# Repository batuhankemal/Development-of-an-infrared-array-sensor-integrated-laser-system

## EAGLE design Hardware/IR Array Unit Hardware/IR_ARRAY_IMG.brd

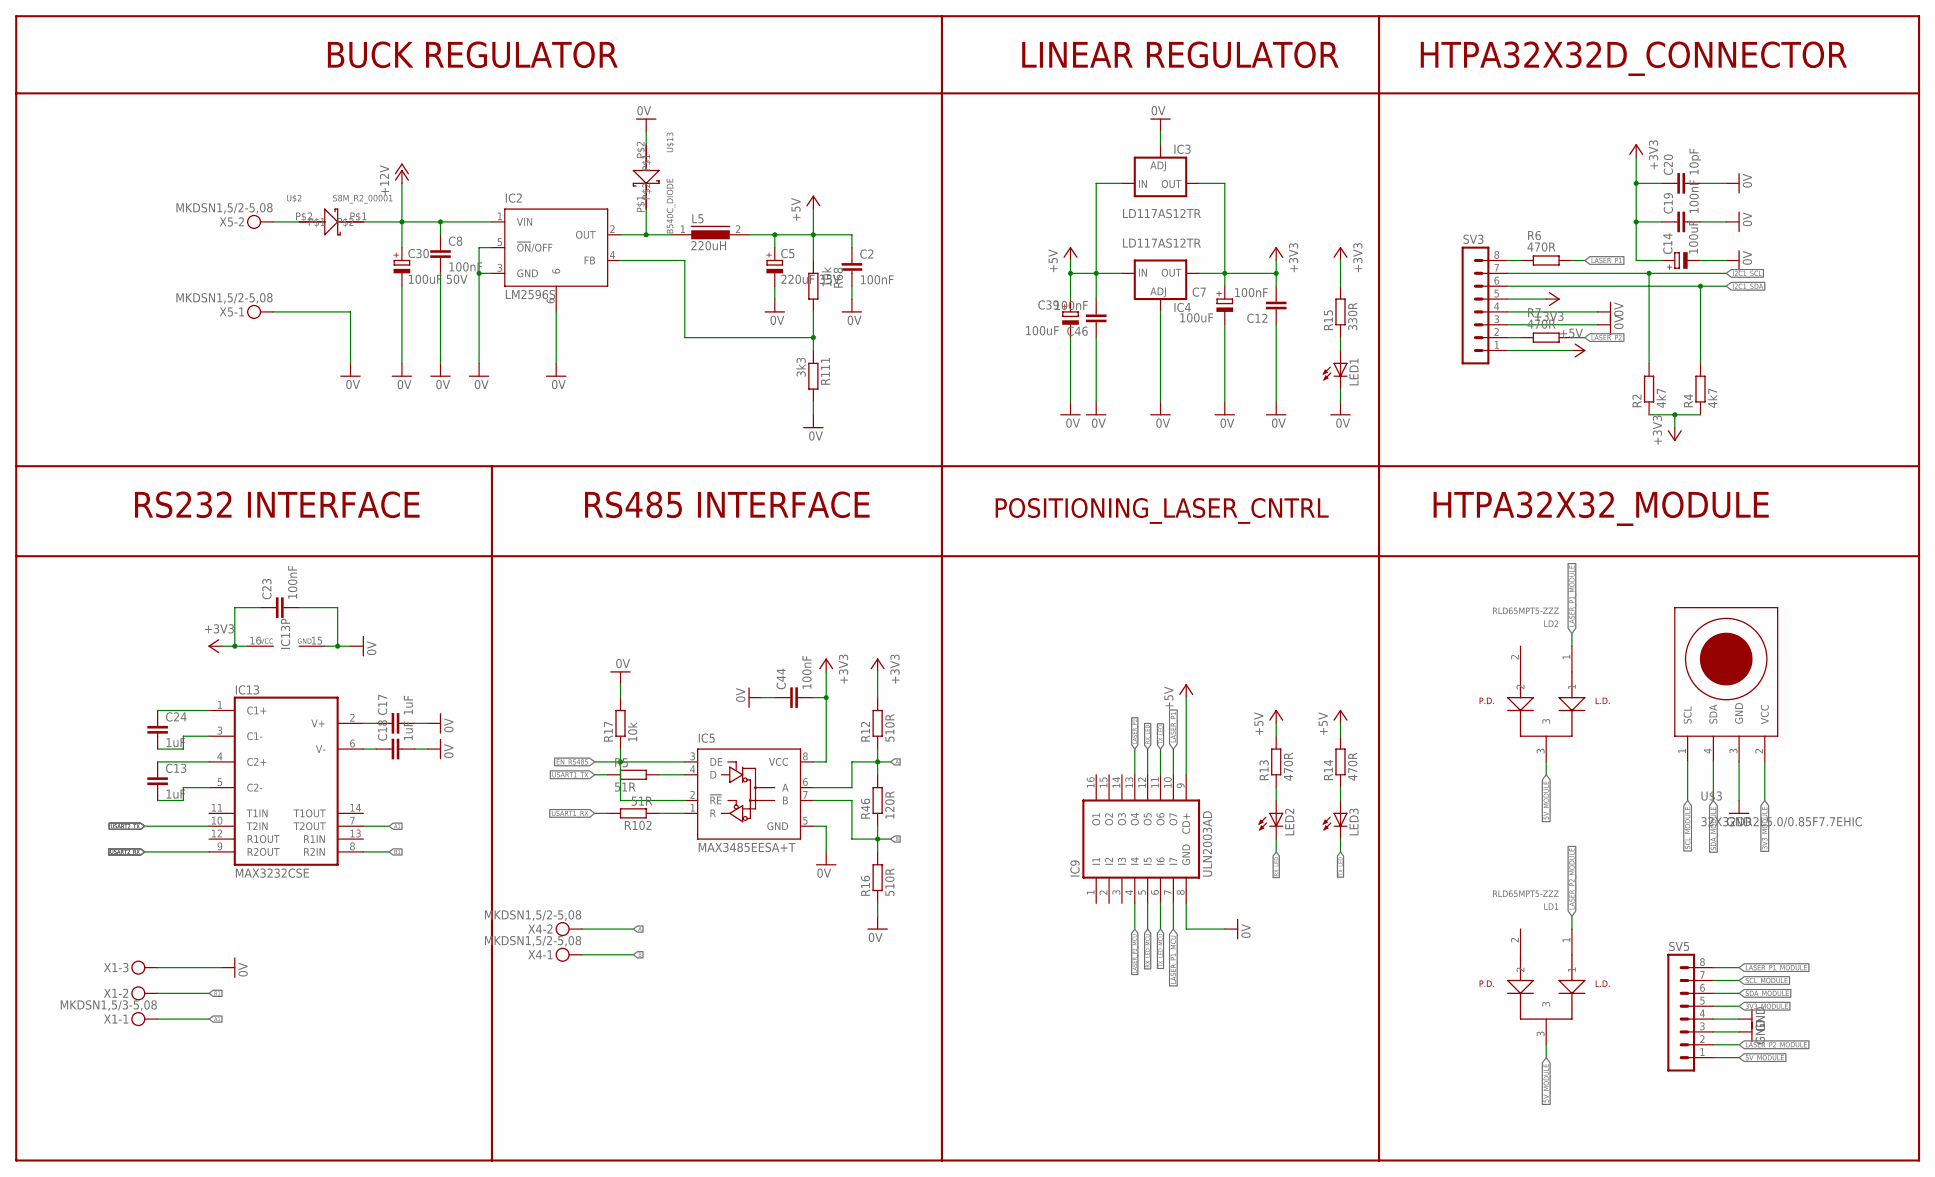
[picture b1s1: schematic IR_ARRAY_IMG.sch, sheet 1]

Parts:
C2, C8: 100nF; C0805
C5: 220uF 35V; 153CLV-0810
C7, C39: 100uF; 153CLV-0605
C12, C19, C23, C44, C46: 100nF; C0603
C13, C17, C18, C24: 1uF; C1206
C14: 100uF; C/6032-28R
C20: 10pF; C0603
C30: 100uF 50V; 153CLV-0810
IC2: LM2596S; TO263-5
IC3, IC4: LD117AS12TR; SOT223
IC5: MAX3485EESA+T; D_R-PDSO-G8
IC9: ULN2003AD; SO16
IC13: MAX3232CSE; SO16
L5: 220uH; DR125
LD1, LD2: RLD65MPT5-ZZZ
LED1, LED2, LED3: LEDCHIPLED_0805; CHIPLED_0805
R2, R4: 4k7; R0603
R5, R102: 51R; R0603
R6, R7: 470R; M0805
R12, R16: 510R; R0603
R13, R14: 470R; R0603
R15: 330R; R0603
R17: 10k; R0603
R46: 120R; R0603
R68: 10k; M0805
R111: 3k3; M0805
SV3, SV5: MA08-1
U$2: S8M_R2_00001; SMC
U$3: 32X32DR2L5.0/0.85F7.7EHIC
U$13: B540C_DIODE; SMC
X1: MKDSN1,5/3-5,08
X4, X5: MKDSN1,5/2-5,08

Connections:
0V: C2.2, C5.-, C7.-, C8.2, C12.1, C14.-, C17.2, C18.2, C19.2, C20.2, C23.2, C30.-, C39.-, C44.1, C46.1, IC2.3 (GND), IC2.5 (!ON!/OFF), IC2.6, IC3.1 (ADJ), IC4.1 (ADJ), IC5.5 (GND), IC9.8 (GND), IC13.15 (GND), LED1.C, R16.1, R17.2, R111.2, SV3.3, SV3.4, U$13.P$2, X1.3, X5.1; also elsewhere on the board
3V3_MODULE: SV5.5, U$3.2 (VCC)
5V_MODULE: LD1.3, LD2.3, SV5.1
+3V3: C7.+, C12.2, C14.+, C19.1, C20.1, C23.1, C44.2, IC3.4 (OUT), IC4.4 (OUT), IC5.8 (VCC), IC13.16 (VCC), R2.1, R4.1, R12.2, R15.2, SV3.5; also elsewhere on the board
+5V: C2.1, C5.+, C39.+, C46.2, IC3.3 (IN), IC4.3 (IN), IC9.9 (CD+), L5.2, R13.2, R14.2, R68.1, SV3.1
+12V: C8.1, C30.+, IC2.1 (VIN), U$2.P$1
A: IC5.6 (A), R12.1, R46.2, X4.2
A1: IC13.7 (T2OUT), X1.1
B: IC5.7 (B), R16.2, R46.1, X4.1
B1: IC13.8 (R2IN), X1.2
EN_RS485: IC5.2 (!RE), IC5.3 (DE), R17.1; also elsewhere on the board
GND: SV5.3, SV5.4, U$3.3 (GND)
I2C1_SCL: R2.2, SV3.7; also elsewhere on the board
I2C1_SDA: R4.2, SV3.6; also elsewhere on the board
LASER_P1: IC9.10 (O7), R6.2
LASER_P1_MCU: IC9.7 (I7); also elsewhere on the board
LASER_P1_MODULE: LD2.1, SV5.8
LASER_P2: IC9.13 (O4), R7.2
LASER_P2_MCU: IC9.4 (I4); also elsewhere on the board
LASER_P2_MODULE: LD1.1, SV5.2
unnamed: U$2.P$2, X5.2
unnamed: C18.1, IC13.6 (V-)
unnamed: R7.1, SV3.2
unnamed: R6.1, SV3.8
unnamed: LED2.A, R13.1
unnamed: LED3.A, R14.1
unnamed: IC5.4 (D), R5.2
unnamed: LED1.A, R15.1
unnamed: C24.1, IC13.1 (C1+)
unnamed: C24.2, IC13.3 (C1-)
unnamed: IC5.1 (R), R102.1
unnamed: C13.1, IC13.4 (C2+)
unnamed: C13.2, IC13.5 (C2-)
unnamed: C17.1, IC13.2 (V+)
unnamed: IC2.2 (OUT), L5.1, U$13.P$1
unnamed: IC2.4 (FB), R68.2, R111.1
RX_LED: IC9.12 (O5), LED2.C
RX_LED_MCU: IC9.5 (I5); also elsewhere on the board
SCL_MODULE: SV5.7, U$3.1 (SCL)
SDA_MODULE: SV5.6, U$3.4 (SDA)
TX_LED: IC9.11 (O6), LED3.C
TX_LED_MCU: IC9.6 (I6); also elsewhere on the board
USART1_RX: R102.2; also elsewhere on the board
USART1_TX: R5.1; also elsewhere on the board
USART2_RX: IC13.9 (R2OUT); also elsewhere on the board
USART2_TX: IC13.10 (T2IN); also elsewhere on the board

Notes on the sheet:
BUCK REGULATOR
LINEAR REGULATOR
RS232 INTERFACE
RS485 INTERFACE
HTPA32X32D_CONNECTOR
HTPA32X32_MODULE
POSITIONING_LASER_CNTRL

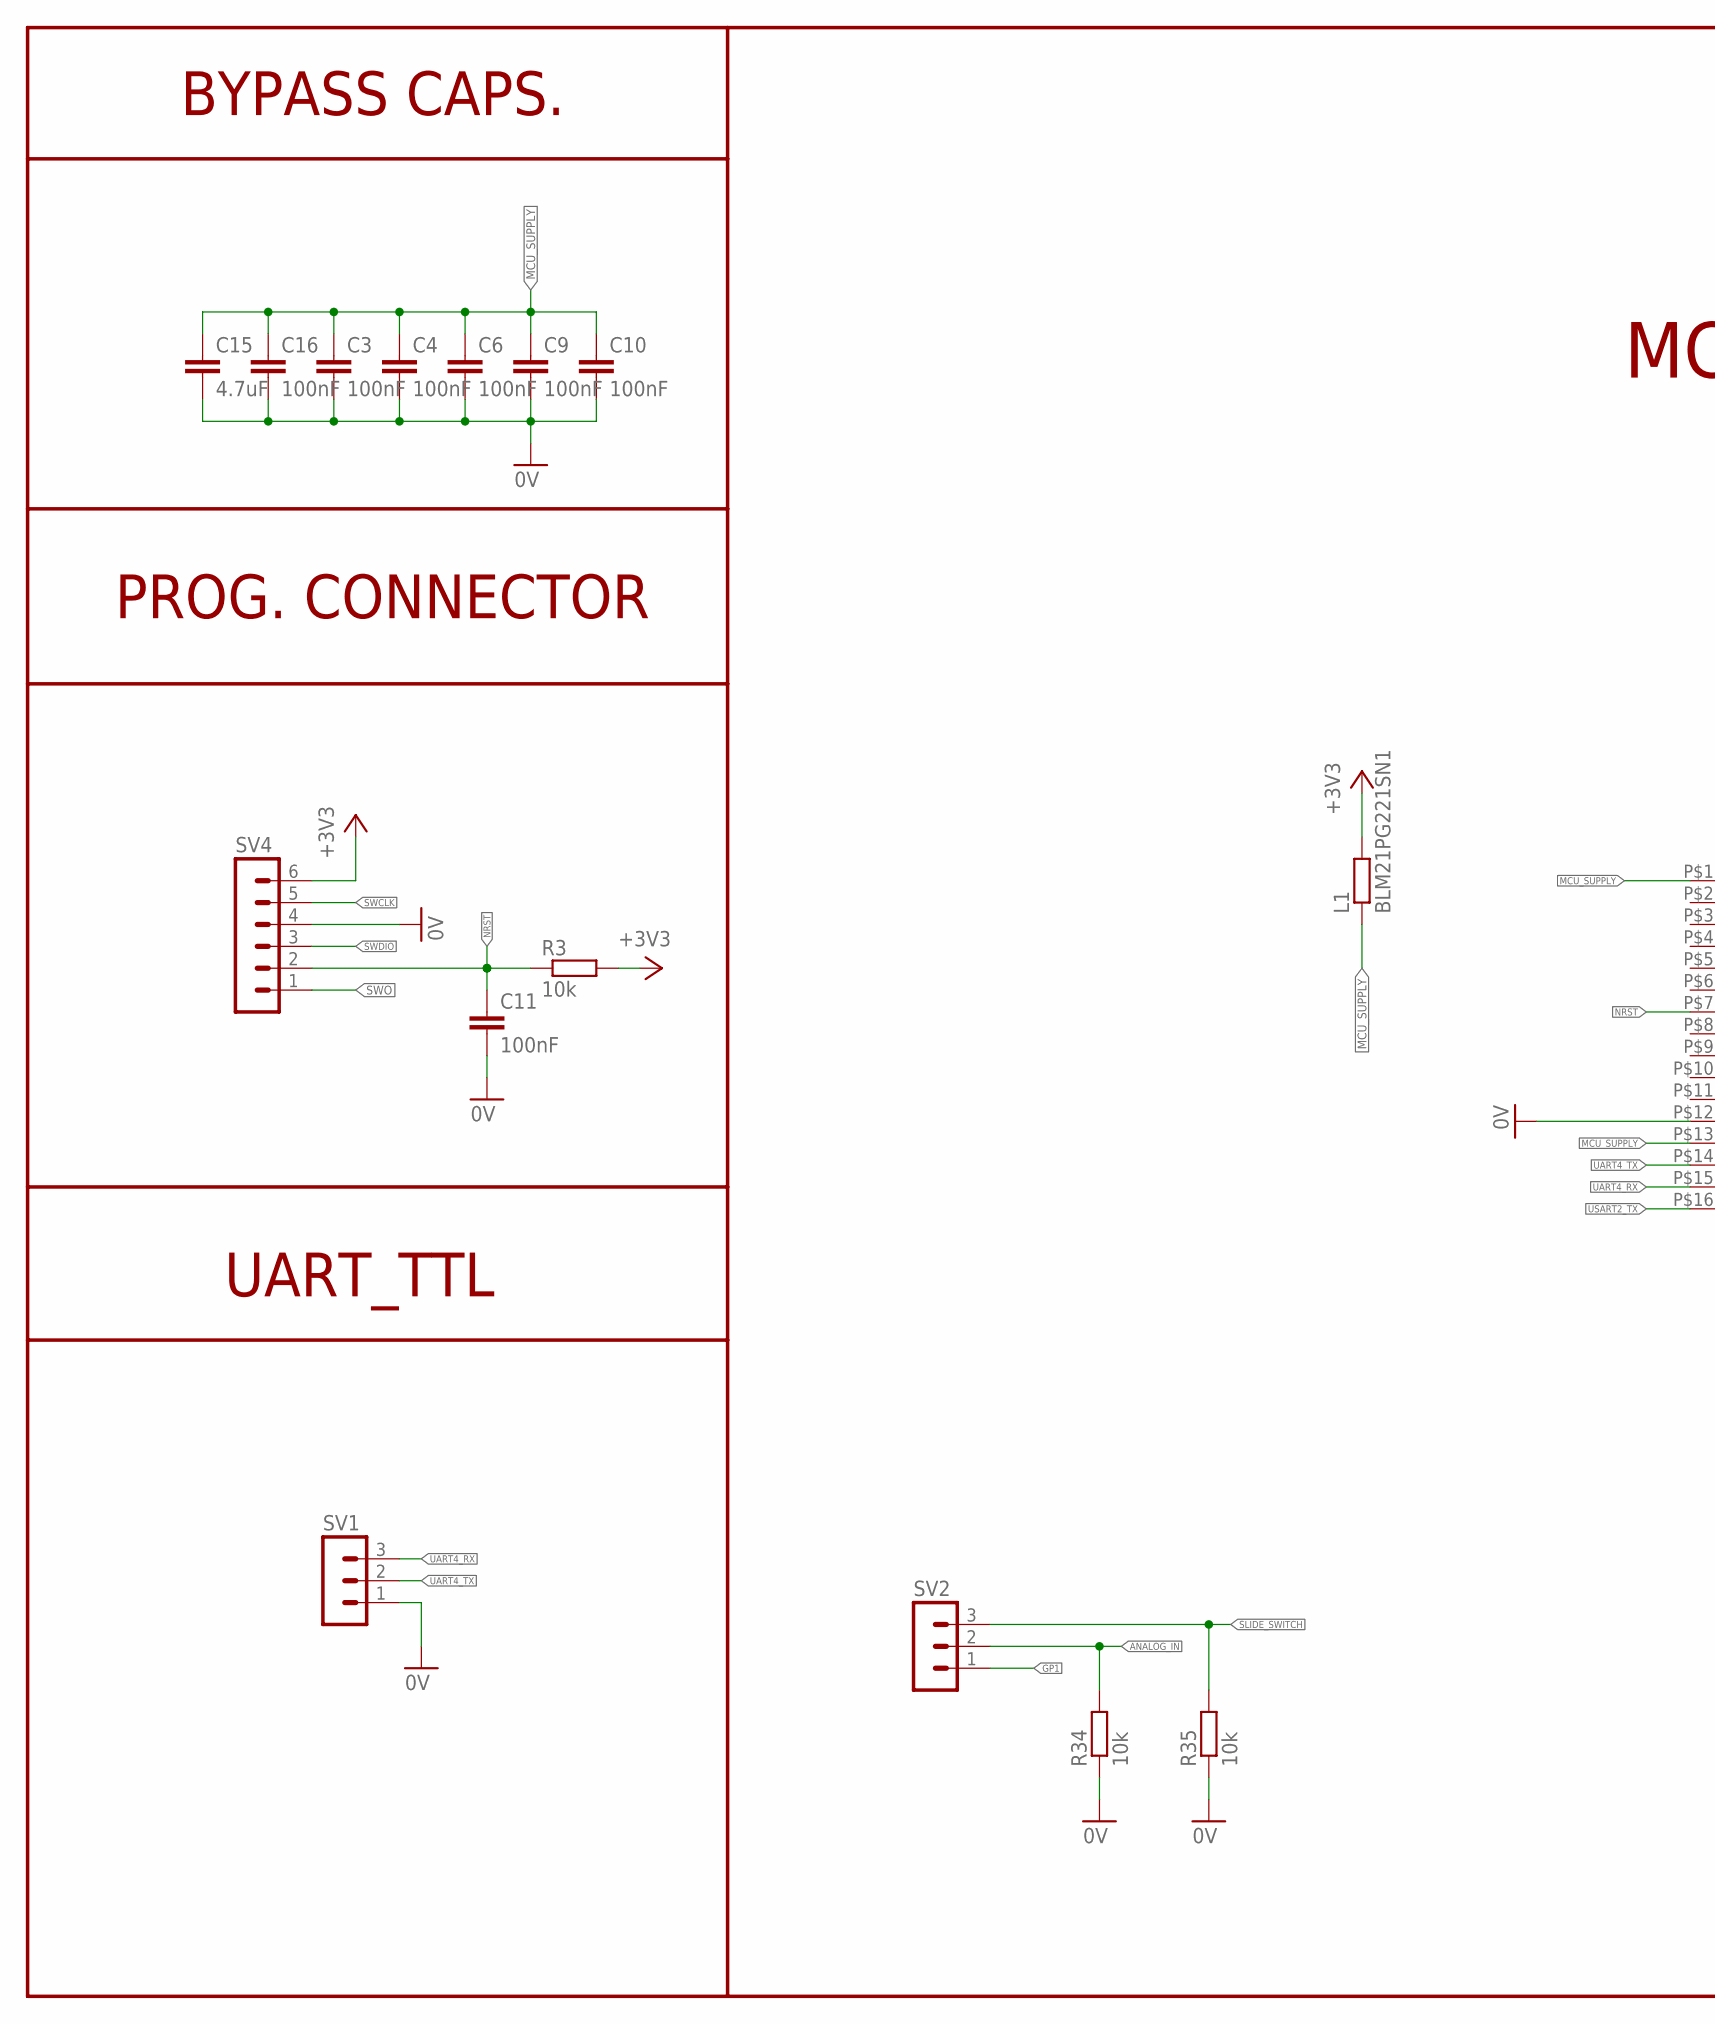
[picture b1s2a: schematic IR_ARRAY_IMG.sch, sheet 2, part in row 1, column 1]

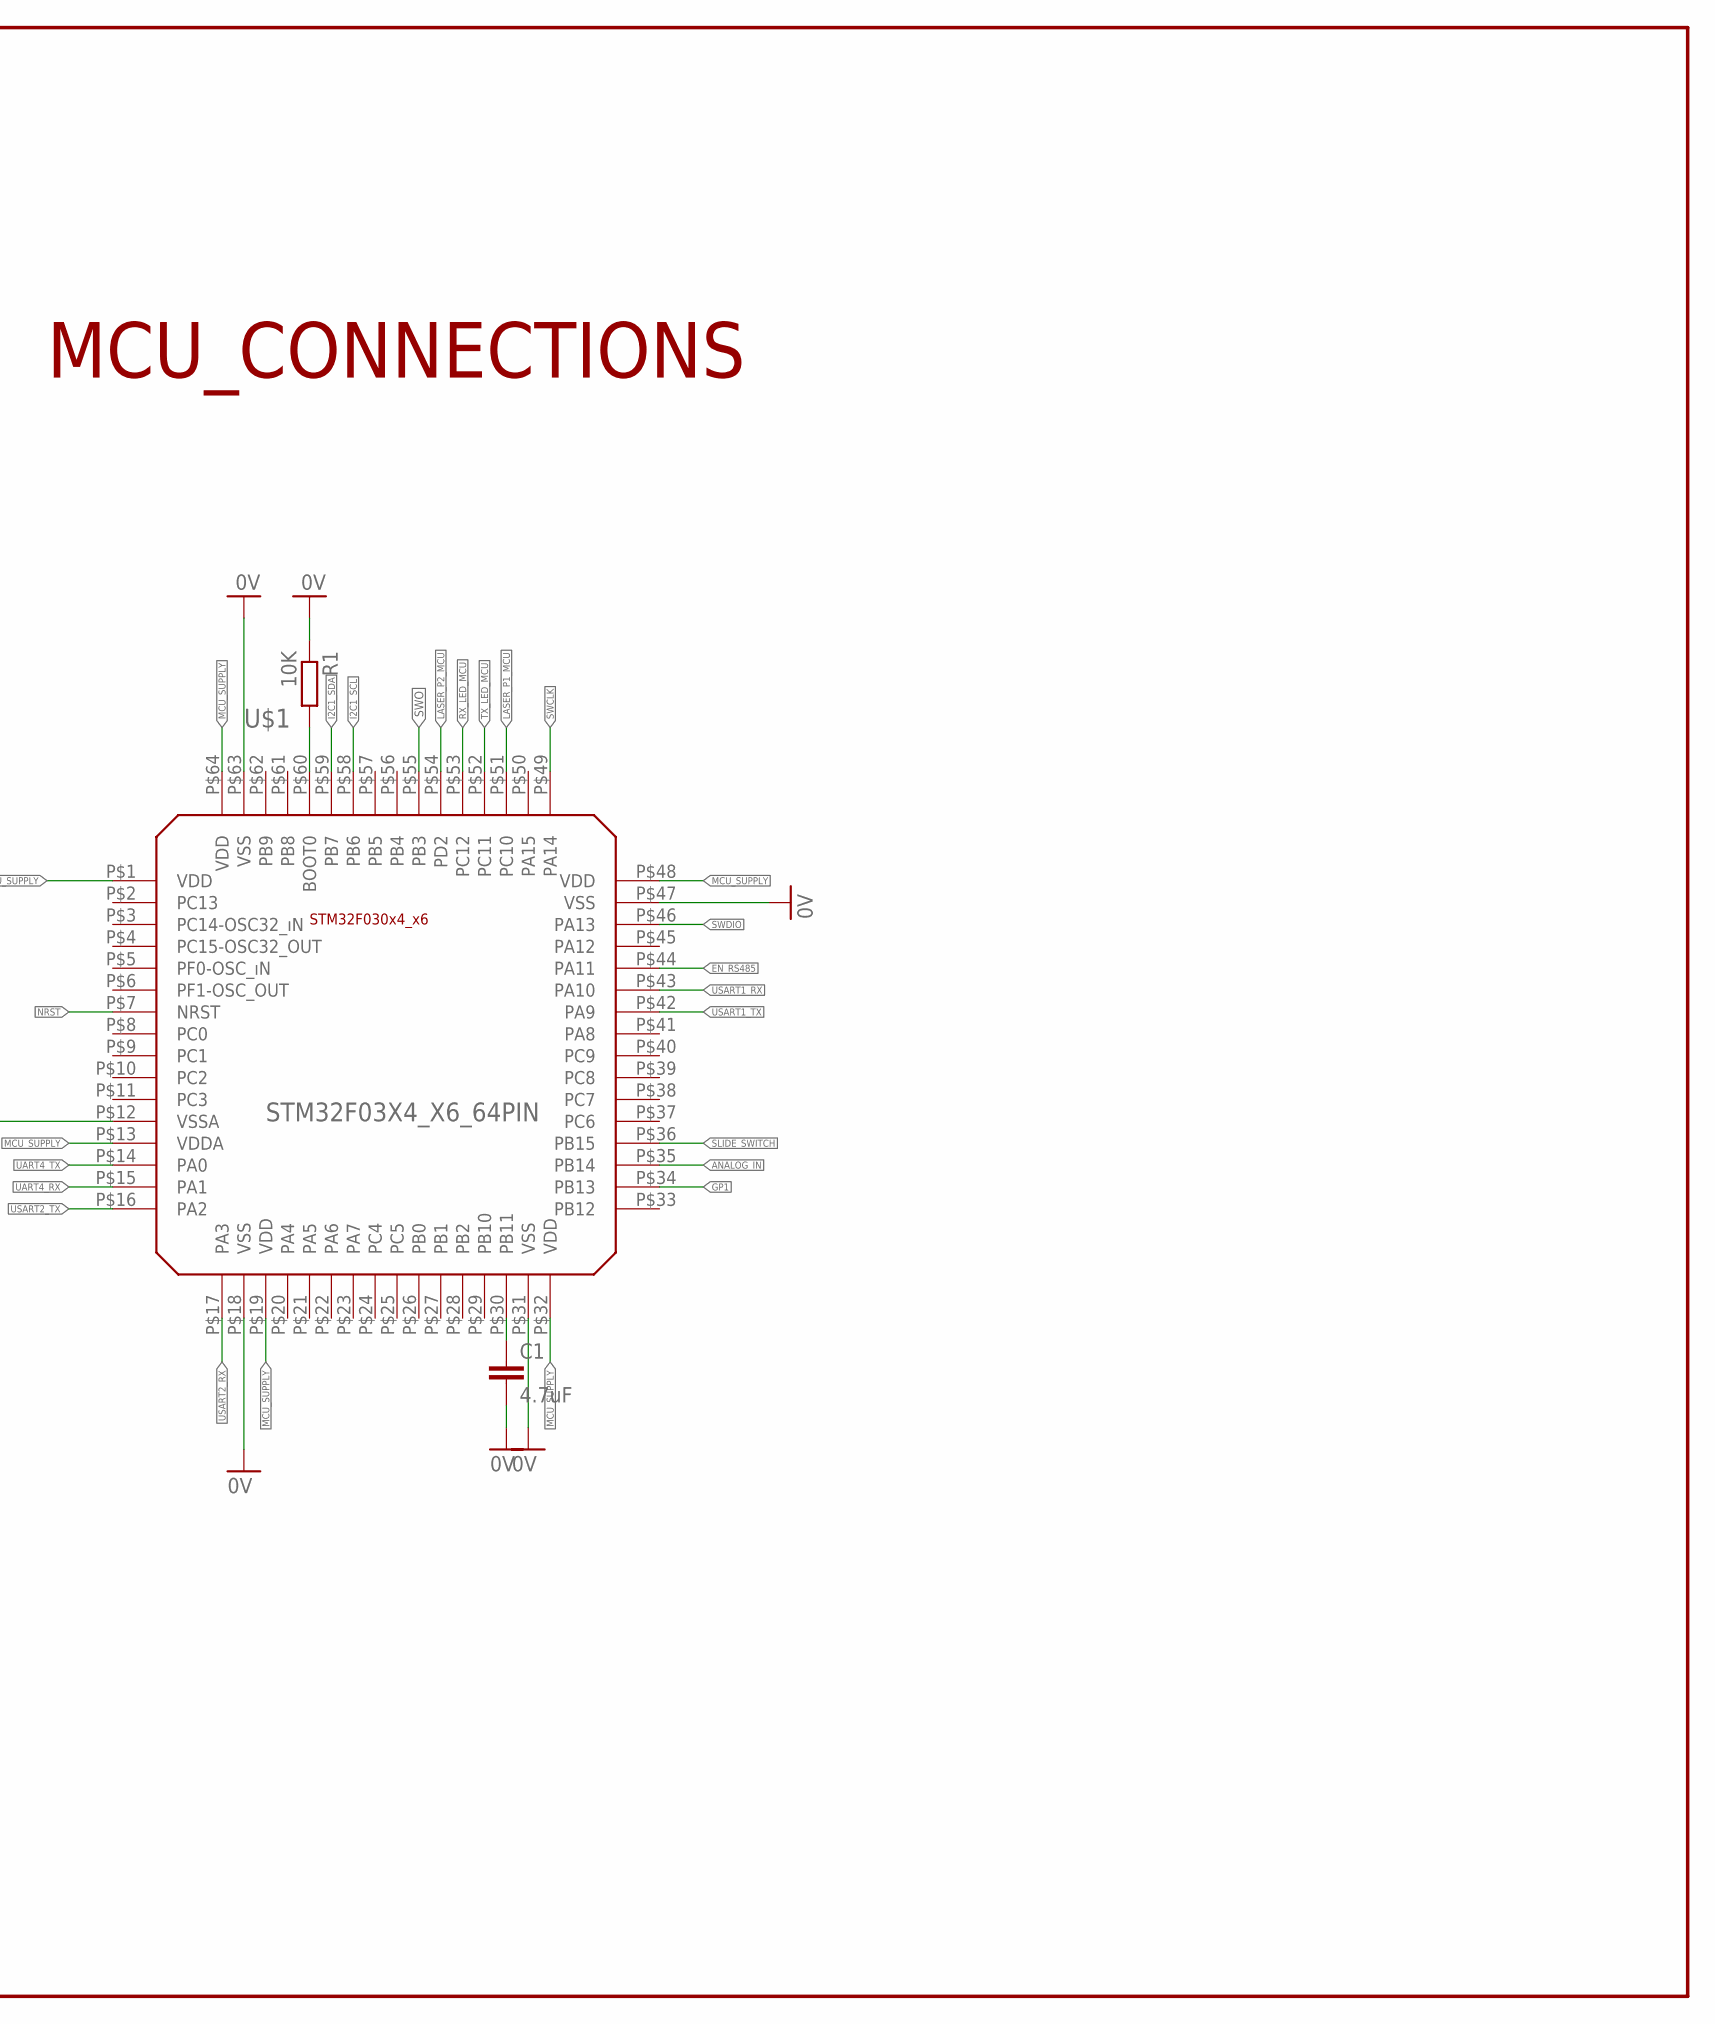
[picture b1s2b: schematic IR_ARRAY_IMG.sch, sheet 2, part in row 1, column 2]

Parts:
C1, C15: 4.7uF; C0805
C3, C4, C6, C9, C10, C11, C16: 100nF; C0603
L1: BLM21PG221SN1; R0805
R1: 10K; R0603
R3, R34, R35: 10k; R0603
SV1, SV2: MA03-1
SV4: MA06-1
U$1: STM32F03X4_X6_64PIN; LQFP64

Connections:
0V: C1.2, C3.2, C4.2, C6.2, C9.2, C10.2, C11.2, C15.2, C16.2, R1.1, R34.1, R35.1, SV1.1, SV4.4, U$1.P$12 (VSSA), U$1.P$18 (VSS), U$1.P$31 (VSS), U$1.P$47 (VSS), U$1.P$63 (VSS); also elsewhere on the board
+3V3: L1.2, R3.2, SV4.6; also elsewhere on the board
ANALOG_IN: R34.2, SV2.2, U$1.P$35 (PB14)
EN_RS485: U$1.P$44 (PA11); also elsewhere on the board
GP1: SV2.1, U$1.P$34 (PB13)
I2C1_SCL: U$1.P$58 (PB6); also elsewhere on the board
I2C1_SDA: U$1.P$59 (PB7); also elsewhere on the board
LASER_P1_MCU: U$1.P$51 (PC10); also elsewhere on the board
LASER_P2_MCU: U$1.P$54 (PD2); also elsewhere on the board
MCU_SUPPLY: C3.1, C4.1, C6.1, C9.1, C10.1, C15.1, C16.1, L1.1, U$1.P$1 (VDD), U$1.P$13 (VDDA), U$1.P$19 (VDD), U$1.P$32 (VDD), U$1.P$48 (VDD), U$1.P$64 (VDD)
unnamed: R1.2, U$1.P$60 (BOOT0)
unnamed: C1.1, U$1.P$30 (PB11)
NRST: C11.1, R3.1, SV4.2, U$1.P$7 (NRST)
RX_LED_MCU: U$1.P$53 (PC12); also elsewhere on the board
SLIDE_SWITCH: R35.2, SV2.3, U$1.P$36 (PB15)
SWCLK: SV4.5, U$1.P$49 (PA14)
SWDIO: SV4.3, U$1.P$46 (PA13)
SWO: SV4.1, U$1.P$55 (PB3)
TX_LED_MCU: U$1.P$52 (PC11); also elsewhere on the board
UART4_RX: SV1.3, U$1.P$15 (PA1)
UART4_TX: SV1.2, U$1.P$14 (PA0)
USART1_RX: U$1.P$43 (PA10); also elsewhere on the board
USART1_TX: U$1.P$42 (PA9); also elsewhere on the board
USART2_RX: U$1.P$17 (PA3); also elsewhere on the board
USART2_TX: U$1.P$16 (PA2); also elsewhere on the board

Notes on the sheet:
BYPASS CAPS.
PROG. CONNECTOR
MCU_CONNECTIONS
UART_TTL

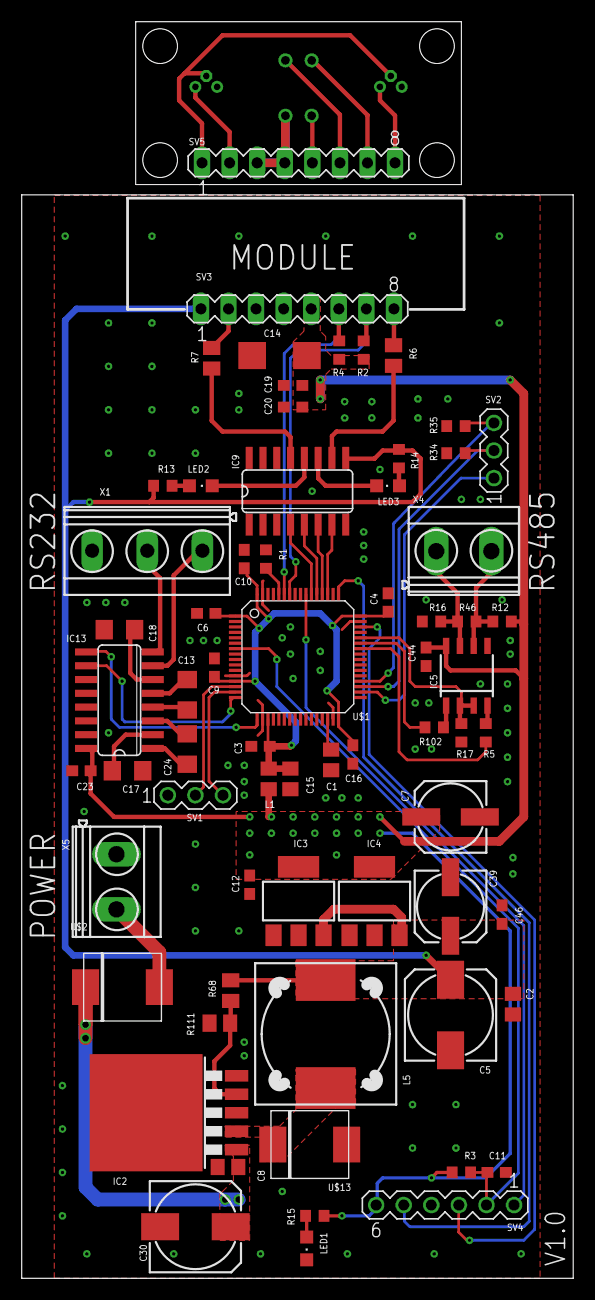
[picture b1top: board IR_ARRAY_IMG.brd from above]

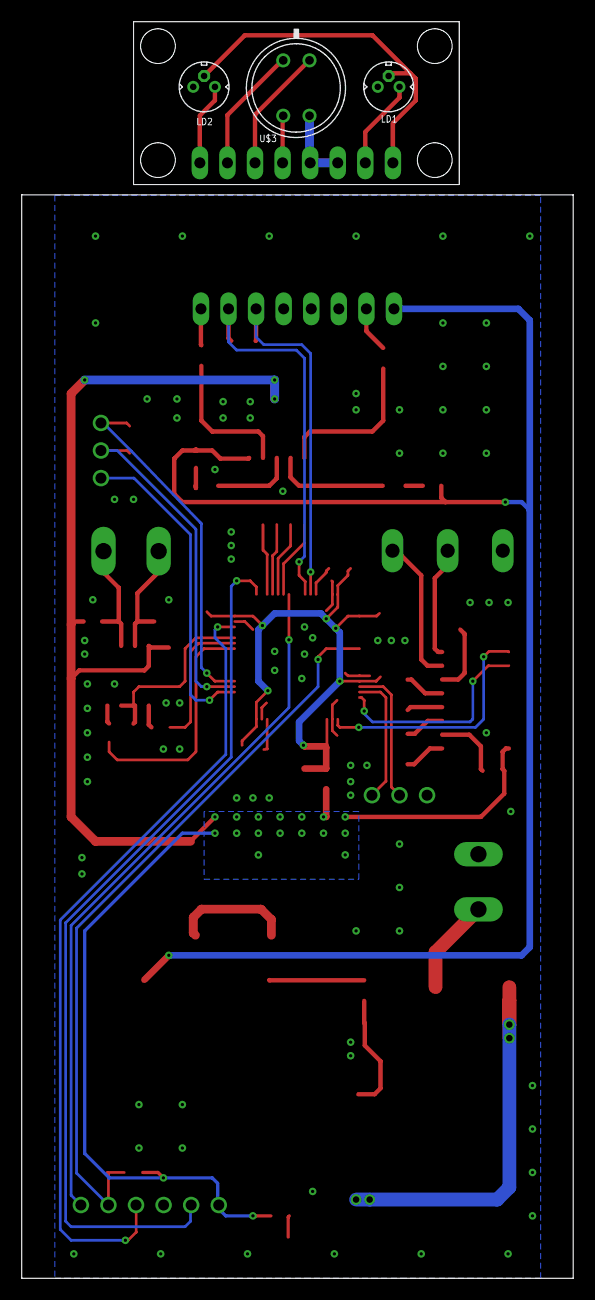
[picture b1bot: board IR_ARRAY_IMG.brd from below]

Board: 2 copper layers, 50.8 x 115.8 mm, 70 parts (3 on the bottom side), 58 nets.

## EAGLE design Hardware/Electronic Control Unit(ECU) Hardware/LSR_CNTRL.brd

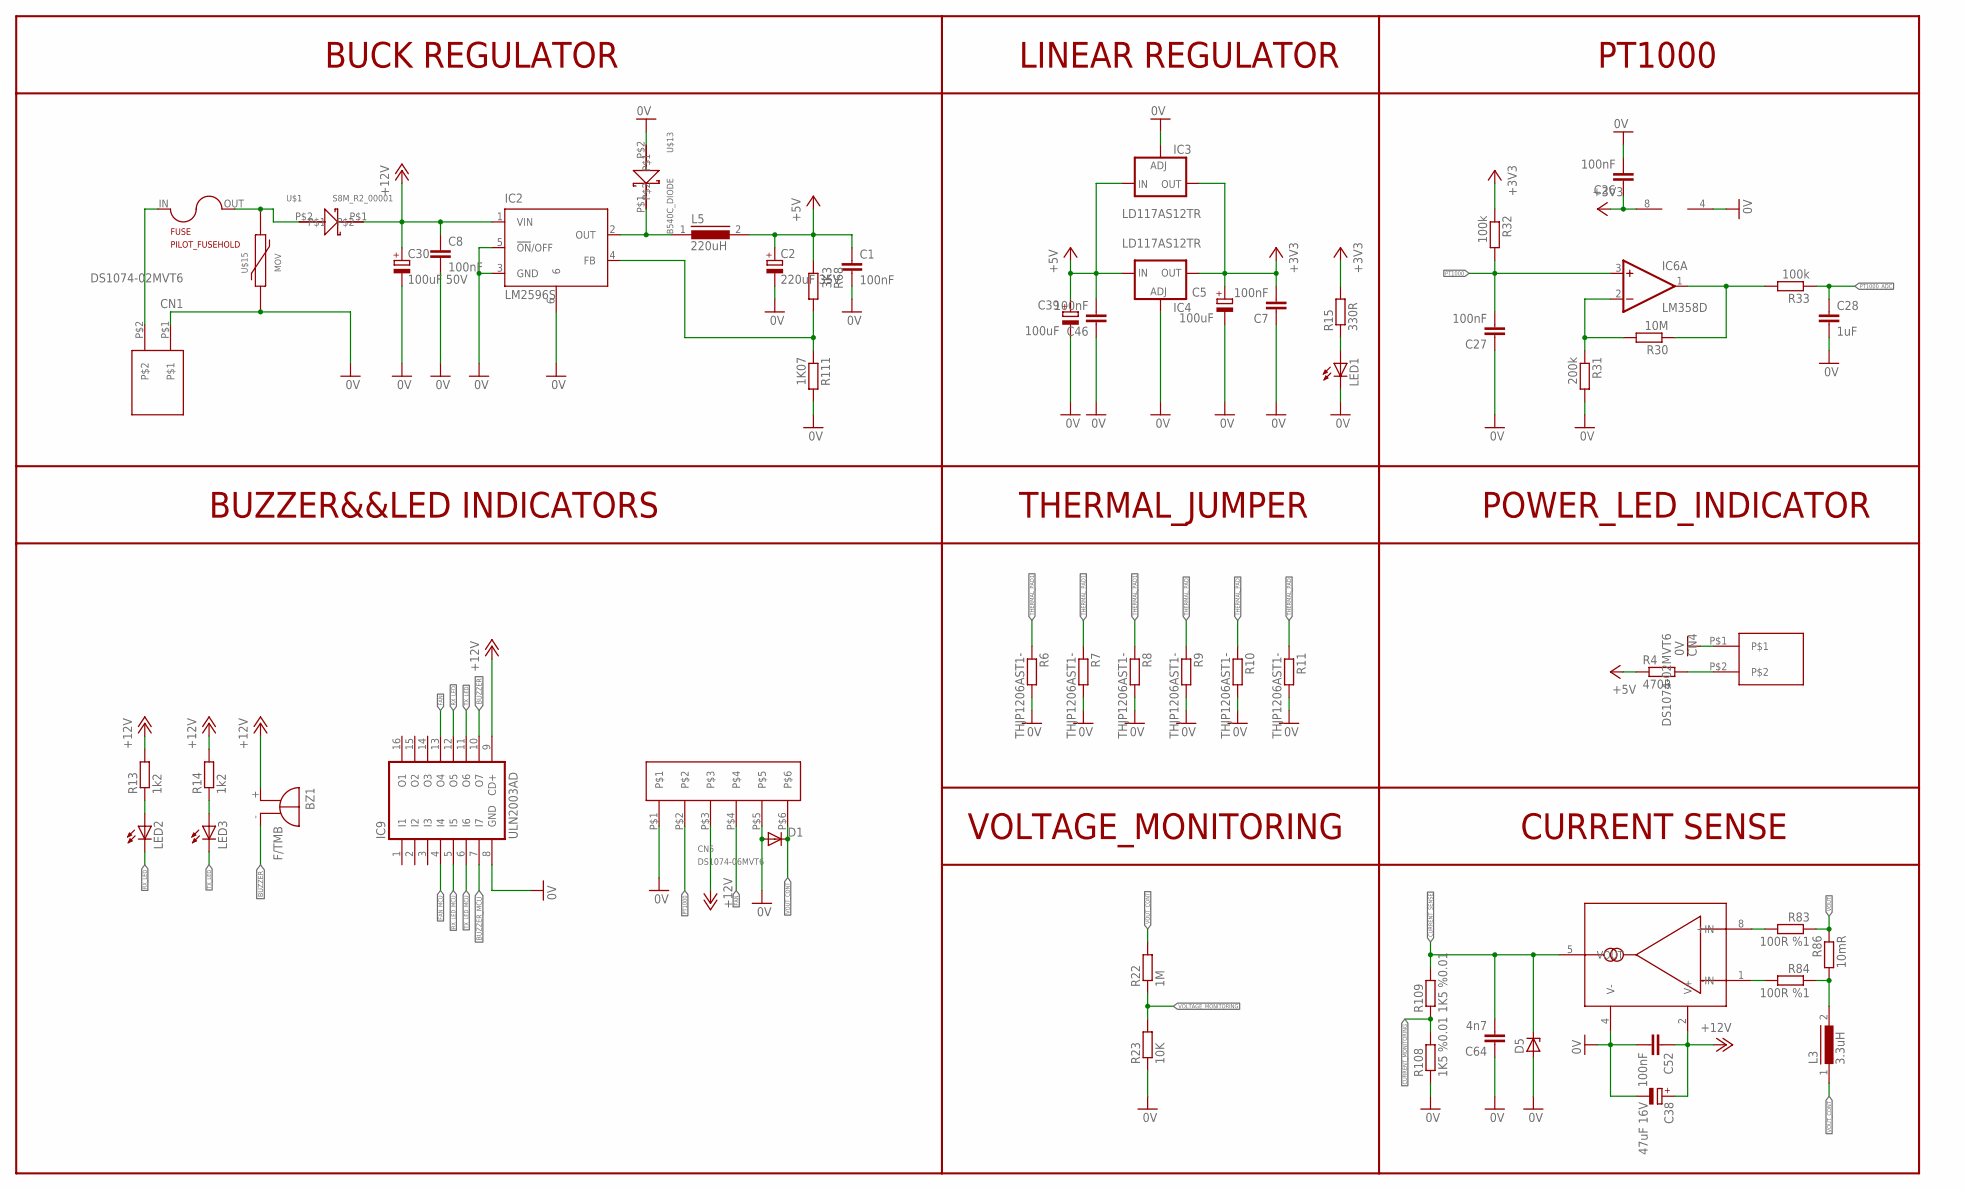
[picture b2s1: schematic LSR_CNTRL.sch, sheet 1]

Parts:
BZ1: F/TMB
C1, C8, C52: 100nF; C0805
C2: 220uF 35V; 153CLV-0810
C5, C39: 100uF; 153CLV-0605
C7, C26, C27, C46: 100nF; C0603
C28: 1uF; C1206
C30: 100uF 50V; 153CLV-0810
C38: 47uF 16V; B/3528-21R
C64: 4n7; C0805
CN1, CN4: DS1074-02MVT6
CN5: DS1074-06MVT6
D1: DIODE-SMB; SMB
D5: ZENER-DIODESOD80C; SOD80C
FUSE: PILOT_FUSEHOLD; RTM_FUSEHOLD
IC2: LM2596S; TO263-5
IC3, IC4: LD117AS12TR; SOT223
IC6: LM358D; SO08
IC9: ULN2003AD; SO16
L3: 3.3uH; DR127
L5: 220uH; DR125
LED1, LED2, LED3: LEDCHIPLED_0805; CHIPLED_0805
R4: 470R; M0805
R6, R7, R8, R9, R10, R11: THJP1206AST1-; M0805
R13, R14: 1k2; R0603
R15: 330R; R0603
R22: 1M; R0603
R23: 10K; R0603
R30: 10M; R0603
R31: 200k; R0603
R32, R33: 100k; R0603
R68: 3K3; M0805
R83, R84: 100R %1; R0805
R86: 10mR; R2512
R108, R109: 1K5 %0.01; R0603
R111: 1K07; M0805
U$1: S8M_R2_00001; SMC
U$5: LT6105; MSOP-8
U$13: B540C_DIODE; SMC
U$15: MOV-10D201K

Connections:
0V: C1.2, C2.-, C5.-, C7.1, C8.2, C26.2, C27.1, C28.2, C30.-, C38.-, C39.-, C46.1, C52.2, C64.1, CN1.P$1, CN4.P$1, CN5.P$1, CN5.P$5, D1.A, D5.A, IC2.3 (GND), IC2.5 (!ON!/OFF), IC2.6, IC3.1 (ADJ), IC4.1 (ADJ), IC6.4 (V-), IC9.8 (GND), LED1.C, R6.2, R7.2, R8.2, R9.2, R10.2, R11.2, R23.1, R31.2, R108.1, R111.2, U$5.4 (V-), U$13.P$2, U$15.1; also elsewhere on the board
+3V3: C5.+, C7.2, C26.1, IC3.4 (OUT), IC4.4 (OUT), IC6.8 (V+), R15.2, R32.1; also elsewhere on the board
+5V: C1.1, C2.+, C39.+, C46.2, IC3.3 (IN), IC4.3 (IN), L5.2, R4.1, R68.1; also elsewhere on the board
+12V: BZ1.+, C8.1, C30.+, C38.+, C52.1, CN5.P$3, IC2.1 (VIN), IC9.9 (CD+), R13.2, R14.2, U$1.P$1, U$5.2 (V+); also elsewhere on the board
BUZZER: BZ1.-, IC9.10 (O7)
BUZZER_MCU: IC9.7 (I7); also elsewhere on the board
CURRENT_MONITORING: R108.2, R109.1; also elsewhere on the board
CURRENT_SENSE: C64.2, D5.C, R109.2, U$5.5 (VOUT)
FAN: CN5.P$4, IC9.13 (O4)
FAN_MCU: IC9.4 (I4); also elsewhere on the board
unnamed: CN1.P$2, FUSE.IN
unnamed: LED2.A, R13.1
unnamed: LED3.A, R14.1
unnamed: FUSE.OUT, U$1.P$2, U$15.2
unnamed: CN4.P$2, R4.2
unnamed: IC6.2 (-IN), R30.2, R31.1
unnamed: LED1.A, R15.1
unnamed: IC6.1 (OUT), R30.1, R33.2
unnamed: L3.2, R84.1, R86.2
unnamed: R83.2, U$5.8 (+IN)
unnamed: R84.2, U$5.1 (-IN)
unnamed: IC2.2 (OUT), L5.1, U$13.P$1
unnamed: IC2.4 (FB), R68.2, R111.1
PT1000: C27.2, CN5.P$2, IC6.3 (+IN), R32.2
PT1000_ADC: C28.1, R33.1; also elsewhere on the board
RX_LED: IC9.12 (O5), LED2.C
RX_LED_MCU: IC9.5 (I5); also elsewhere on the board
THERMAL_PAD: R9.1, R10.1, R11.1
THERMAL_PAD1: R6.1, R7.1, R8.1
TX_LED: IC9.11 (O6), LED3.C
TX_LED_MCU: IC9.6 (I6); also elsewhere on the board
VOLTAGE_MONITORING: R22.1, R23.2; also elsewhere on the board
VOUT: R83.1, R86.1; also elsewhere on the board
VOUT_CONT: CN5.P$6, D1.C, L3.1, R22.2

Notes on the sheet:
BUCK REGULATOR
LINEAR REGULATOR
PT1000
POWER_LED_INDICATOR
CURRENT SENSE
THERMAL_JUMPER
VOLTAGE_MONITORING
BUZZER&&LED INDICATORS
